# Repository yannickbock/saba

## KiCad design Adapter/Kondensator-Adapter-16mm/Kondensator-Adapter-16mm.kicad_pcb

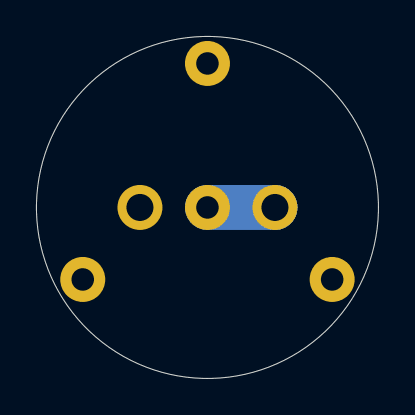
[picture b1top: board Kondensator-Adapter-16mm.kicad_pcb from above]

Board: 2 copper layers, 19.0 x 19.0 mm, 6 parts (0 on the bottom side), 2 nets.

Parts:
J1, J2, J3, J4, J5, J6: Conn_01x01; SolderWirePad_single_1-2mmDrill

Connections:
GND: J2.1, J3.1, J4.1, J6.1
VCC: J1.1, J5.1

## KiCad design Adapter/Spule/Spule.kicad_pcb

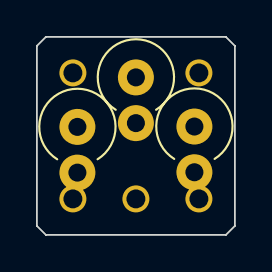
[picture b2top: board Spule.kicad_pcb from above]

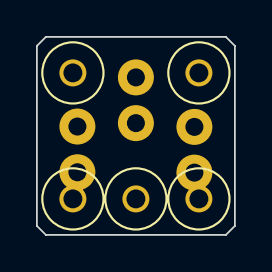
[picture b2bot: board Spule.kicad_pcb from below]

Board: 2 copper layers, 11.0 x 11.0 mm, 8 parts (5 on the bottom side), 4 nets, no tracks yet.

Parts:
J1, J2, J3, J4, J5: Conn_01x01; TestPoint_Plated_Hole_D2.0mm
L1, L2, L3: L; L_Axial_L9.5mm_D4.0mm_P2.54mm_Vertical_Fastron_SMCC

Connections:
unnamed: J1.1, L1.2
unnamed: J2.1, L3.2
unnamed: L2.1, L3.1
unnamed: L1.1, L2.2

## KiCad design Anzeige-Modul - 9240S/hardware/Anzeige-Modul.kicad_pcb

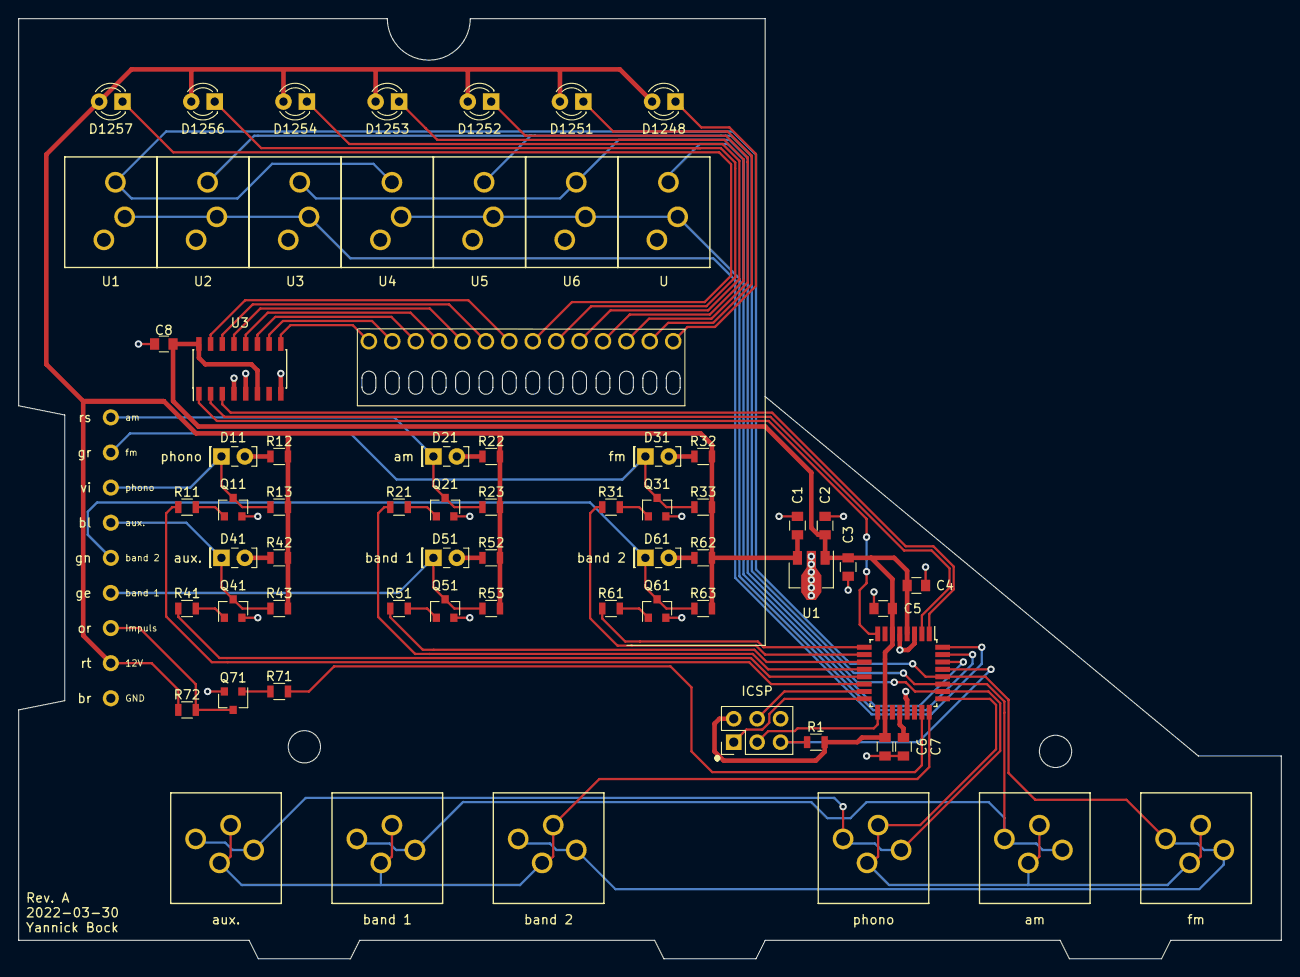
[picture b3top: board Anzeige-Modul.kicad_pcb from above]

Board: 2 copper layers, 137.0 x 102.0 mm, 68 parts (0 on the bottom side), 60 nets.

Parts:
C1: 330nF; C_0805
C2, C4, C5, C6, C7, C8: 100nF; C_0805
C3: 2.2µF; C_0805
D11, D21, D31, D41, D51, D61: LED; LED_Rectangular_W5.0mm_H2.0mm
D1248, D1251, D1252, D1253, D1254, D1256, D1257: LED; LED_D3.0mm
J1: Conn_01x09_Male; PadArray_3.81mm_01x09
J3: Conn_02x03_Counter_Clockwise; Pin_Header_Straight_2x03_Pitch2.54mm
J5: Conn_01x14_Male; PadArray_2.54mm_01x14
Q11, Q21, Q31, Q41, Q51, Q61, Q71: BC847; SOT-23
R1, R11, R21, R31, R41, R51, R61, R71: 1k; R_0805
R12, R22, R32, R42, R52, R62: 680; R_0805
R13, R23, R33, R43, R53, R63: 100k; R_0805
R72: 2k7; R_0805
SW1: AUX; saba_92xx_push_button
SW2: BD1; saba_92xx_push_button
SW3: BD2; saba_92xx_push_button
SW4: PHONO; saba_92xx_push_button
SW5: AM; saba_92xx_push_button
SW6: FM; saba_92xx_push_button
SW7: U1; SW_PUSH_SPDT
SW8: U2; SW_PUSH_SPDT
SW9: U3; SW_PUSH_SPDT
SW10: U4; SW_PUSH_SPDT
SW11: U5; SW_PUSH_SPDT
SW12: U6; SW_PUSH_SPDT
SW13: U; SW_PUSH_SPDT
U1: L78L05_SOT89; SOT-89-3
U2: ATmega328P-AU; TQFP-32_7x7mm_Pitch0.8mm
U3: 74HC138; SOIC-16_3.9x9.9mm_Pitch1.27mm

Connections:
+5V: C2.2, C3.2, C4.2, C5.2, C6.2, C8.2, J3.2, R1.1, U1.1, U2.4, U2.6, U2.18, U3.6, U3.16
+12V: C1.2, D1248.2, D1251.2, D1252.2, D1253.2, D1254.2, D1256.2, D1257.2, J1.8, R12.2, R13.2, R22.2, R23.2, R32.2, R33.2, R42.2, R43.2, R52.2, R53.2, R62.2, R63.2, R72.1, U1.3
A0: U2.8, U3.1
A1: U2.2, U3.2
A2: U2.1, U3.3
AM: R21.1, U2.12
AUX: R41.1, U2.13
BD1: R51.1, U2.11
BD2: R61.1, U2.9
CLK: J3.3, U2.17
FM: R31.1, U2.10
GND: C1.1, C2.1, C3.1, C4.1, C5.1, C6.1, C7.2, C8.1, J1.9, J3.6, Q11.2, Q21.2, Q31.2, Q41.2, Q51.2, Q61.2, Q71.2, U1.2, U2.3, U2.5, U2.21, U3.4, U3.5, U3.8
IMPULS: R71.1, U2.23
KD_1_IN: SW1.2, SW1.4, SW4.2, SW4.4, SW9.1, SW12.1, U2.26
KD_1_OUT: SW1.1, SW1.3, SW2.1, SW2.3, SW3.1, SW3.3, U2.24
KD_2_IN: SW2.2, SW2.4, SW5.2, SW5.4, SW8.1, SW11.1, U2.27
KD_2_OUT: SW4.1, SW4.3, SW5.1, SW5.3, SW6.1, SW6.3, U2.25
KD_3_IN: SW3.2, SW3.4, SW6.2, SW6.4, SW7.1, SW10.1, U2.28
KD_3_OUT: SW7.2, SW8.2, SW9.2, U2.32
KD_4_IN: SW13.1, U2.30
KD_4_OUT: SW10.2, SW11.2, SW12.2, SW13.2, U2.31
M1: J5.1, U3.9
M2: J5.2, U3.10
M3: J5.3, U3.11
M4: J5.4, U3.12
M5: J5.5, U3.13
M6: J5.6, U3.14
M7: J5.7, U3.15
M8: D1257.1, J5.8
M9: D1256.1, J5.9
M10: D1254.1, J5.10
M11: D1253.1, J5.11
M12: D1252.1, J5.12
M13: D1251.1, J5.13
M14: D1248.1, J5.14
MISO: J3.1, U2.16
MOSI: J3.4, U2.15
unnamed: C7.1, U2.20
unnamed: D11.1, J1.3, Q11.3, R13.1
unnamed: D11.2, R12.1
unnamed: D21.1, J1.1, Q21.3, R23.1
unnamed: D21.2, R22.1
unnamed: D31.1, J1.2, Q31.3, R33.1
unnamed: D31.2, R32.1
unnamed: D41.1, J1.4, Q41.3, R43.1
unnamed: D41.2, R42.1
unnamed: D51.1, J1.6, Q51.3, R53.1
unnamed: D51.2, R52.1
unnamed: D61.1, J1.5, Q61.3, R63.1
unnamed: D61.2, R62.1
unnamed: J1.7, Q71.3, R72.2
unnamed: Q11.1, R11.2
unnamed: Q21.1, R21.2
unnamed: Q31.1, R31.2
unnamed: Q41.1, R41.2
unnamed: Q51.1, R51.2
unnamed: Q61.1, R61.2
unnamed: Q71.1, R71.2
PHONO: R11.1, U2.14
RESET: J3.5, R1.2, U2.29
